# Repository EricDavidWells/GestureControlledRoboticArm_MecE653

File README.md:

# Realtime Force Myography
Using the gesture controlled robotic arm developed at [HACKED2019](https://github.com/MarkSherstan/HACKED2019) the project advanced to optimize a force myography (FMG) sensor and algorithm package that can be used to robustly control upper limb prosthetics in real time.

## Background
Although there are many multifunctional hands available for prosthesis use, commercial devices are unable to utilize them largely due to restricted control interfaces. Recent research has focused on improving pattern recognition algorithms to decode electromyographic signals (EMG) into multi degree of freedom movements to enable more robust control. Although results are promising in laboratory conditions, this technique has been unable to be transferred into commercial devices. This is largely due to current surface mounted EMG sensors having inherent unpredictable issues that affect the algorithm’s performance such as cross-talk, electrical interference, muscle fatigue effects, perspiration effects, and skin impedance. An alternative to this technology for use in prosthetics is force myography (FMG). This technology seeks to exploit the deformation resulting from residual muscle movement to obtain prosthesis control. This is typically done in a very similar manner to EMG; however, instead of measuring electrical activity, an array of pressure sensors wrapped around the user’s arm measures muscle deformation. The measured sensor values act as inputs into a pattern recognition algorithm to predict the desired motions from the user. An FMG sensor and algorithm package was designed and optimized to implement robust, real time control of a simulated prosthetic device. Two iterations of prototyping have been achieved, with the second design resulting in a wireless, low profile wristband containing 11 force sensitive resistors (FSR) sensors and an inertial measurement unit (IMU) capable of sampling up to 200 Hz.

## Photos
### Wireless Armband with 11 FSR's, IMU, and Custom PCB
<p align="center">

### Coordinate Frame on Arm
<p align="center">

### Gestures
<p align="center">

### Raw Signals (Left Time Series - Right Spectral Series)
<p align="center">

### Classified Signals PCA Representation 
<p align="center">

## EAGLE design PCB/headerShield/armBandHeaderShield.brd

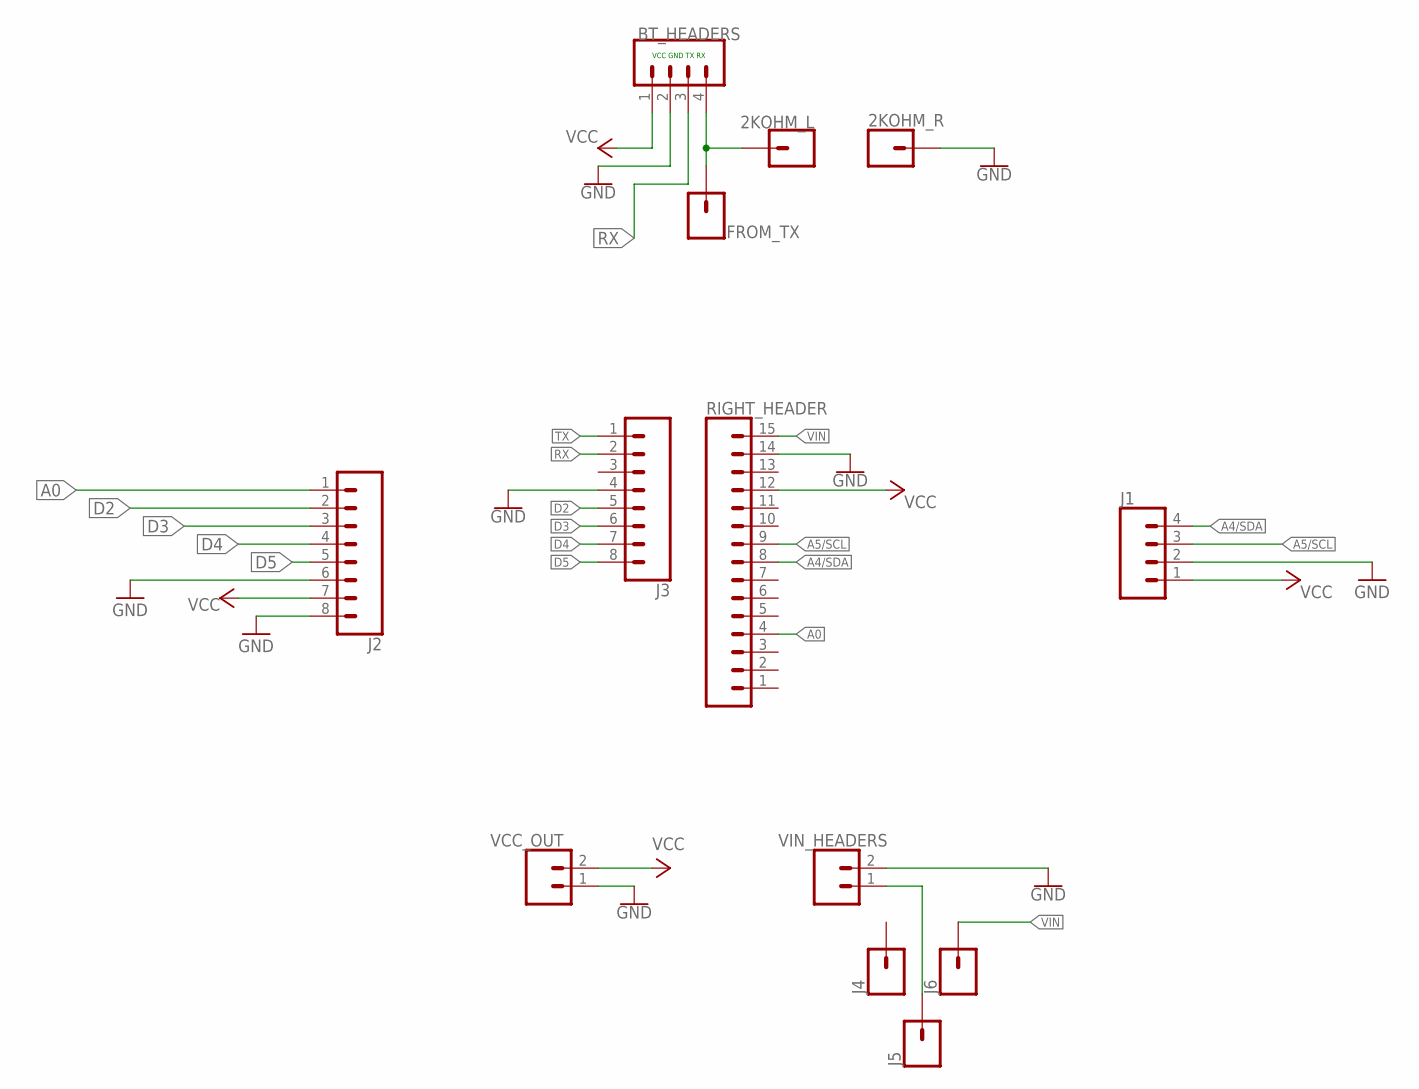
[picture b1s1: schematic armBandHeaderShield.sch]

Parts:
2KOHM_L, 2KOHM_R: CONN_01; 1X01
BT_HEADERS: CONN_04; 1X04
FROM_TX: CONN_01; 1X01
J1: CONN_04; 1X04
J2, J3: CONN_08"; 1X08
J4, J5, J6: CONN_01; 1X01
RIGHT_HEADER: CONN_15; 1X15
VCC_OUT: CONN_02PTH3; 1X02_LONGPADS
VIN_HEADERS: CONN_02PTH3; 1X02_LONGPADS

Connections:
A0: J2.1, RIGHT_HEADER.4
A4/SDA: J1.4, RIGHT_HEADER.8
A5/SCL: J1.3, RIGHT_HEADER.9
D2: J2.2, J3.5
D3: J2.3, J3.6
D4: J2.4, J3.7
D5: J2.5, J3.8
GND: 2KOHM_R.1, BT_HEADERS.2, J1.2, J2.6, J2.8, J3.4, RIGHT_HEADER.14, VCC_OUT.1, VIN_HEADERS.2
unnamed: J5.1, VIN_HEADERS.1
unnamed: 2KOHM_L.1, BT_HEADERS.4, FROM_TX.1
RX: BT_HEADERS.3, J3.2
TX: J3.1
VCC: BT_HEADERS.1, J1.1, J2.7, RIGHT_HEADER.12, VCC_OUT.2
VIN: J6.1, RIGHT_HEADER.15

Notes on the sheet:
VCC GND TX RX

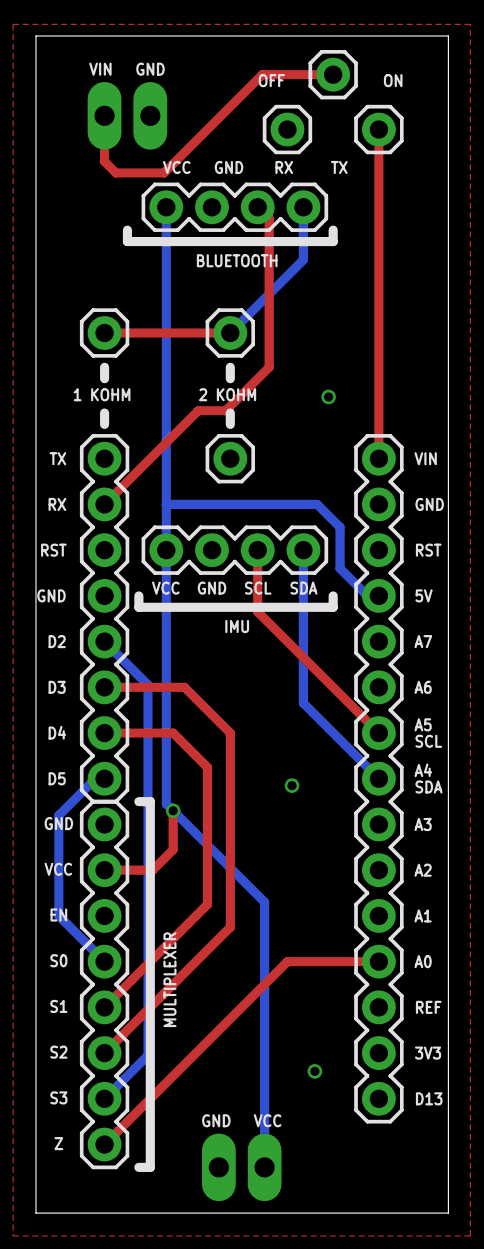
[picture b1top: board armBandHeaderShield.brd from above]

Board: 2 copper layers, 22.9 x 65.4 mm, 13 parts (0 on the bottom side), 13 nets.

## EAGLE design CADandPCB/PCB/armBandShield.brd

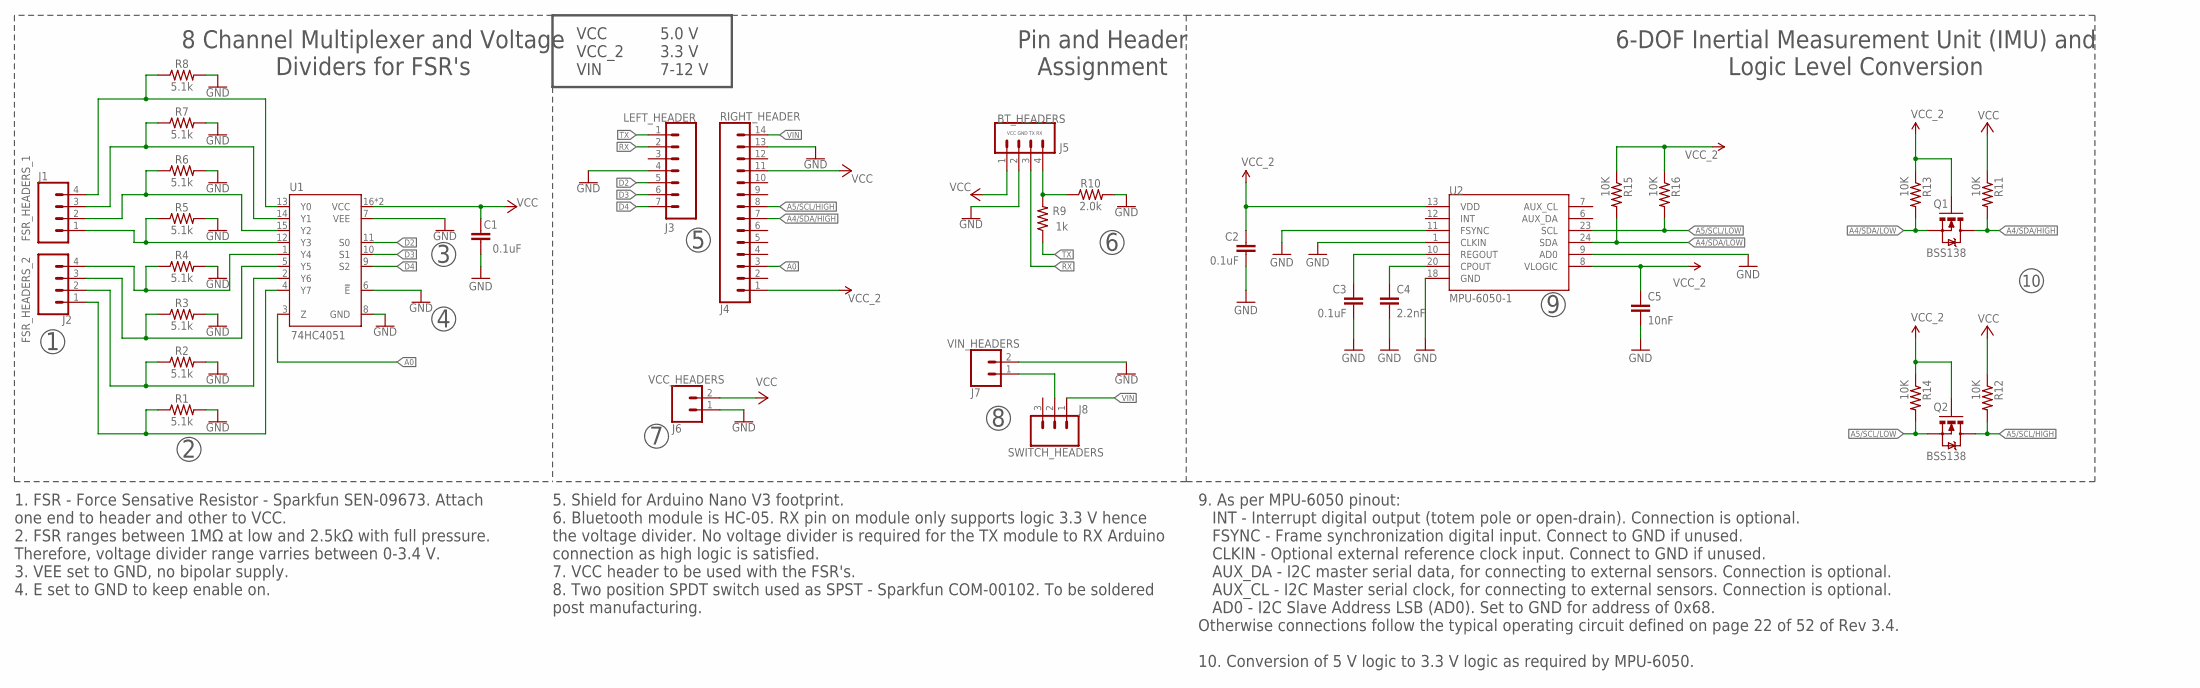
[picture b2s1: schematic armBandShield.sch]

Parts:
74HC4051: U1; DHVQFN-16-2.5X3.5MM
BT_HEADERS: J5; 1X04
C1, C2, C3: 0.1uF; 0603-CAP
C4: 2.2nF; 0603
C5: 10nF; 0603
J1: FSR_HEADERS_1; 1X04
J2: FSR_HEADERS_2; 1X04
LEFT_HEADER: J3; 1X07
Q1, Q2: BSS138; SOT23-3
R1, R2, R3, R4, R5, R6, R7, R8: 5.1k; 0603
R9: 1k; 0603
R10: 2.0k; 0603
R11, R12, R13, R14, R15, R16: 10K; 0603-RES
RIGHT_HEADER: J4; 1X14
SWITCH_HEADERS: J8; 1X03
U2: MPU-6050-1; QFN-24-4MM2
VCC_HEADERS: J6; 1X02_LONGPADS
VIN_HEADERS: J7; 1X02_LONGPADS

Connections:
A0: 74HC4051.3 (Z), RIGHT_HEADER.3
A4/SDA/HIGH: Q1.3 (D), R11.2, RIGHT_HEADER.7
A4/SDA/LOW: Q1.2 (S), R13.2, R15.2, U2.24 (SDA)
A5/SCL/HIGH: Q2.3 (D), R12.2, RIGHT_HEADER.8
A5/SCL/LOW: Q2.2 (S), R14.2, R16.2, U2.23 (SCL)
D2: 74HC4051.11 (S0), LEFT_HEADER.5
D3: 74HC4051.10 (S1), LEFT_HEADER.6
D4: 74HC4051.9 (S2), LEFT_HEADER.7
FSR1: 74HC4051.4 (Y7), J2.1, R1.1
FSR2: 74HC4051.2 (Y6), J2.2, R2.1
FSR3: 74HC4051.5 (Y5), J2.3, R3.1
FSR4: 74HC4051.1 (Y4), J2.4, R4.1
FSR5: 74HC4051.12 (Y3), J1.1, R5.1
FSR6: 74HC4051.15 (Y2), J1.2, R6.1
FSR7: 74HC4051.14 (Y1), J1.3, R7.1
FSR8: 74HC4051.13 (Y0), J1.4, R8.1
GND: 74HC4051.6 (!E!), 74HC4051.7 (VEE), 74HC4051.8 (GND), BT_HEADERS.2, C1.2, C2.2, C3.2, C4.2, C5.2, LEFT_HEADER.4, R1.2, R2.2, R3.2, R4.2, R5.2, R6.2, R7.2, R8.2, R10.2, RIGHT_HEADER.13, U2.1 (CLKIN), U2.9 (AD0), U2.11 (FSYNC), U2.18 (GND), VCC_HEADERS.1, VIN_HEADERS.2
unnamed: SWITCH_HEADERS.2, VIN_HEADERS.1
unnamed: C4.1, U2.20 (CPOUT)
unnamed: C3.1, U2.10 (REGOUT)
unnamed: BT_HEADERS.4, R9.2, R10.1
RX: BT_HEADERS.3, LEFT_HEADER.2
TX: LEFT_HEADER.1, R9.1
VCC: 74HC4051.16 (VCC), 74HC4051.EP (VCC), BT_HEADERS.1, C1.1, R11.1, R12.1, RIGHT_HEADER.11, VCC_HEADERS.2
VCC_2: C2.1, C5.1, Q1.1 (G), Q2.1 (G), R13.1, R14.1, R15.1, R16.1, RIGHT_HEADER.1, U2.8 (VLOGIC), U2.13 (VDD)
VIN: RIGHT_HEADER.14, SWITCH_HEADERS.1

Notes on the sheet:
VCC GND TX RX
8 Channel Multiplexer and Voltage Dividers for FSR's
1. FSR - Force Sensative Resistor - Sparkfun SEN-09673. Attach one end to header and other to VCC. 2. FSR ranges between 1MΩ at low and 2.5kΩ with full pressure. Therefore, voltage divider range varries between 0-3.4 V. 3. VEE set to GND, no bipolar supply. 4. E set to GND to keep enable on.
Pin and Header Assignment
6-DOF Inertial Measurement Unit (IMU) and Logic Level Conversion
5. Shield for Arduino Nano V3 footprint. 6. Bluetooth module is HC-05. RX pin on module only supports logic 3.3 V hence the voltage divider. No voltage divider is required for the TX module to RX Arduino connection as high logic is satisfied. 7. VCC header to be used with the FSR's. 8. Two position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
VCC VCC_2 VIN
5.0 V 3.3 V 7-12 V
9. As per MPU-6050 pinout: INT - Interrupt digital output (totem pole or open-drain). Connection is optional. FSYNC - Frame synchronization digital input. Connect to GND if unused. CLKIN - Optional external reference clock input. Connect to GND if unused. AUX_DA - I2C master serial data, for connec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

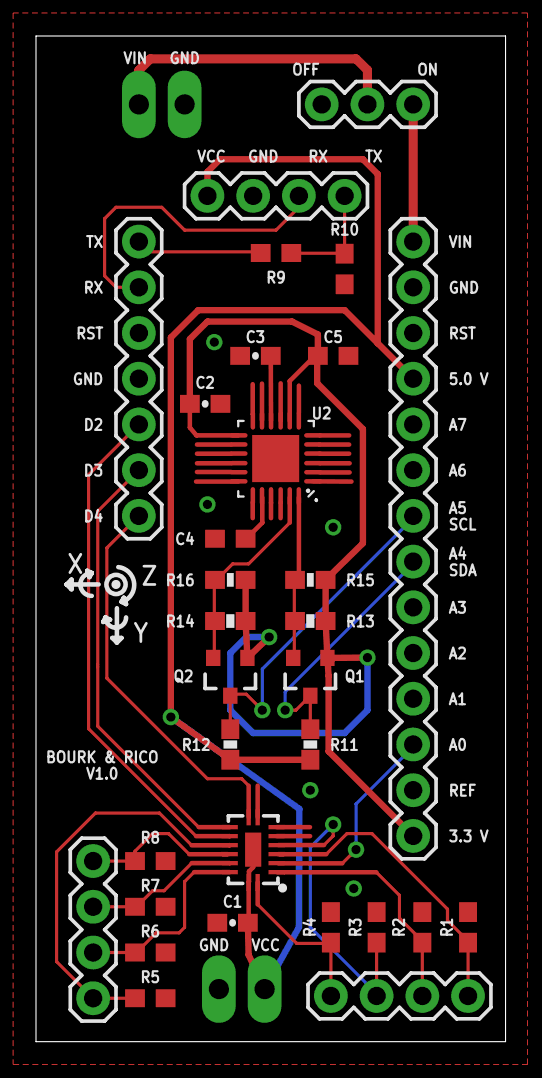
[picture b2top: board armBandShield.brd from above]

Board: 2 copper layers, 26.1 x 55.9 mm, 33 parts (0 on the bottom side), 26 nets.

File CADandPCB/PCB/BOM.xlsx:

Designator | Value | Manufacturer Part # | DIGI-KEY Part # | Qty | Cost / Unit | % Extra | Total Qty | Total Cost | Notes | Link
R1,R2,R3,R4,R5,R6,R7,R8 | 5.1 k | ERJ-3EKF5101V | P5.10KHCT-ND | 8 | 9.8000000000000004E-2 | 5 | 40 | 3.92 | Price Break! | https://www.digikey.ca/product-detail/en/ERJ-3EKF5101V/P5.10KHCT-ND
R9 | 1 k | ERJ-3EKF1001V | P1.00KHCT-ND | 1 | 9.8000000000000004E-2 | 10 | 10 | 0.98 | Price Break! | https://www.digikey.ca/product-detail/en/ERJ-3EKF1001V/P1.00KHCT-ND
R10 | 2 k | ERJ-3EKF2001V | P2.00KHCT-ND | 1 | 9.8000000000000004E-2 | 10 | 10 | 0.98 | Price Break! | https://www.digikey.ca/product-detail/en/ERJ-3EKF2001V/P2.00KHCT-ND
R11,R12,R13,R14,R15,R16 | 10 k | ERJ-3EKF1002V | P10.0KHCT-ND | 6 | 9.8000000000000004E-2 | 8 | 48 | 4.7040000000000006 | Price Break! | https://www.digikey.ca/product-detail/en/ERJ-3EKF1002V/P10.0KHCT-ND
C1,C2,C3 | 0.1 uF | CL10B104KB8NNNC | 1276-1000-1-ND | 3 | 4.7E-2 | 7 | 21 | 0.98699999999999999 | Price Break! | https://www.digikey.ca/product-detail/en/CL10B104KB8NNNC/127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
C4 | 2.2 nF | CL10B222JB8NNNC | 1276-1987-1-ND | 1 | 0.06 | 10 | 10 | 0.6 | Price Break! | https://www.digikey.ca/product-detail/en/CL10B222JB8NNNC/127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
C5 | 10 nF | CL10B103KB8NNNC | 1276-1009-1-ND | 1 | 5.1999999999999998E-2 | 10 | 10 | 0.52 | Price Break! | https://www.digikey.ca/product-detail/en/CL10B103KB8NNNC/127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
Q1,Q2 | - | BSS138 | BSS138CT-ND | 2 | 0.39600000000000002 | 5 | 10 | 3.96 | Price Break! | https://www.digikey.ca/product-detail/en/on-semiconductor/BS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
U1 | - | 74HC4051BQ,115 | 1727-6049-1-ND | 1 | 0.58799999999999997 | 10 | 10 | 5.88 | Price Break! | https://www.digikey.ca/product-detail/en/nexperia-usa-inc/74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
U2 | - | MPU-6050 | 1428-1007-1-ND | 1 | 11.007999999999999 | 5 | 5 | 55.039999999999992 | Price Break! | https://www.digikey.ca/product-detail/en/tdk-invensense/MPU-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
 |  |  |  |  |  |  | Total | 77.570999999999998
Other | Qty | Cost / Unit | Total Cost | Link
MPU 6050 breakout!! | 1 | 14.47 | 14.47 | https://www.digikey.ca/product-detail/en/dfrobot/SEN0142/173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
 | 2 | 12.05 | 24.1 | https://www.digikey.ca/product-detail/en/trinamic-motion-con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
 | 1 | 30.13 | 30.13 | https://www.digikey.ca/product-detail/en/trinamic-motion-con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
 |  | Total | 68.7
$100 Free Shipping
HC-05????
FSR
10^-6 micro µ | 0.0022 pF
10^-9 nano n | 2.2 nF
10^-12 pico p | 2200 uF

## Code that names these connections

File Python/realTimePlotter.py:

# Adapted from: https://www.thepoorengineer.com/en/arduino-python-plot/
from threading import Thread
import serial
import time
import collections
import matplotlib.pyplot as plt
import matplotlib.animation as animation
import struct
import copy


class serialPlot:
    def __init__(self, serialPort, serialBaud, plotLength, dataNumBytes, numSignals):
        self.port = serialPort
        self.baud = serialBaud
        self.plotMaxLength = plotLength
        self.dataNumBytes = dataNumBytes
        self.numSignals = numSignals
        self.rawData = bytearray(numSignals * dataNumBytes)
        self.dataType = None

        if dataNumBytes == 2:
            self.dataType = 'h'

        self.data = []
        for i in range(numSignals):
            self.data.append(collections.deque([0] * plotLength, maxlen=plotLength))

        self.isRun = True
        self.isReceiving = False
        self.thread = None
        self.plotTimer = 0
        self.previousTimer = 0

        print('Trying to connect to: ' + str(serialPort) + ' at ' + str(serialBaud) + ' BAUD.')
        try:
            self.serialConnection = serial.Serial(serialPort, serialBaud, timeout=4)
            print('Connected to ' + str(serialPort) + ' at ' + str(serialBaud) + ' BAUD.')
        except:
            print("Failed to connect with " + str(serialPort) + ' at ' + str(serialBaud) + ' BAUD.')

    def readSerialStart(self):
        if self.thread == None:
            self.thread = Thread(target=self.backgroundThread)
            self.thread.start()
            # Block till we start receiving values
            while self.isReceiving != True:
                time.sleep(0.1)

    def getSerialData(self, frame, lines, lineValueText, lineLabel, timeText):
        currentTimer = time.perf_counter()
        self.plotTimer = int((currentTimer - self.previousTimer) * 1000)
        self.previousTimer = currentTimer
        timeText.set_text('Plot Interval = ' + str(self.plotTimer) + ' ms')
        privateData = copy.deepcopy(self.rawData[:])
        for i in range(self.numSignals):
            data = privateData[(i*self.dataNumBytes):(self.dataNumBytes + i*self.dataNumBytes)]
            value,  = struct.unpack(self.dataType, data)
            self.data[i].append(value)
            lines[i].set_data(range(self.plotMaxLength), self.data[i])
            lineValueText[i].set_text('[' + lineLabel[i] + '] = ' + str(value))

    def backgroundThread(self):
        time.sleep(2)
        self.serialConnection.reset_input_buffer()

        while (self.isRun):
            if (struct.unpack('B', self.serialConnection.read())[0] is 0x9F) and (struct.unpack('B', self.serialConnection.read())[0] is 0x6E):
                self.rawData = self.serialConnection.read(self.numSignals * self.dataNumBytes)
                self.isReceiving = True

    def close(self):
        self.isRun = False
        self.thread.join()
        self.serialConnection.close()
        print('Disconnected...')



def main():
    portName = '/dev/cu.wchusbserial1410'
    baudRate = 115200
    maxPlotLength = 100
    dataNumBytes = 2
    numSignals = 8

    s = serialPlot(portName, baudRate, maxPlotLength, dataNumBytes, numSignals)
    s.readSerialStart()

    pltInterval = 20
    xmin = 0
    xmax = maxPlotLength
    ymin = 0
    ymax = 1024

    fig = plt.figure(figsize=(12, 6))
    ax = plt.axes(xlim=(xmin, xmax), ylim=(float(ymin - (ymax - ymin) / 10), float(ymax + (ymax - ymin) / 10)))
    ax.set_title("FSR Live Output",fontweight='bold',size=20)
    ax.set_xlabel("Time -->",fontweight='bold')
    ax.set_ylabel("Raw Analog Out",fontweight='bold')

    lineLabel = ['FSR1', 'FSR2', 'FSR3', 'FSR4', 'FSR5', 'FSR6', 'FSR7', 'FSR8']
    style = ['c-', 'm-', 'y-', '-k', '--c', '--m', '--y', '--k']
    timeText = ax.text(0.80, 0.95, '', transform=ax.transAxes)
    lines = []
    lineValueText = []
    for i in range(numSignals):
        lines.append(ax.plot([], [], style[i], label=lineLabel[i])[0])
        lineValueText.append(ax.text(0.05, 0.95-i*0.05, '', transform=ax.transAxes))

    anim = animation.FuncAnimation(fig, s.getSerialData, fargs=(lines, lineValueText, lineLabel, timeText), interval=pltInterval)    # fargs has to be a tuple

    plt.legend(loc='upper center', ncol=4)
    plt.xticks([])
    plt.show()

    s.close()


if __name__ == '__main__':
    main()

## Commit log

2019-01-28 Added Training Function and Data Visualization Function
2019-01-28 Added main script to call all functions
2019-01-28 Remove .asv files and make .gitignore
2019-01-28 Servo kill switch, display messages, readability
2019-01-28 General cleanup
2019-01-28 Add stateVisualizer to display the state instead of command line.
2019-01-28 Performance increase for visualizer.
2019-01-28 Fix ... and \c warning in main and training functions
2019-01-28 Added variable classes to visualize data
2019-02-05 Add component data sheets for pinout.
2019-02-06 Commit 9250 data sheet
2019-02-15 Initial commit of Eagle files
2019-02-16 Commit robotArm printing resources
2019-02-16 Add eagle backup to gitignore.
2019-02-16 Clean up schematic using labels. Remove old board. Prepare for breakout.
2019-02-16 Added required breakout components for MPU 9250
2019-02-16 Added required breakout components for Multixplexer
2019-02-16 Initial board lay out and .brd commit
2019-02-16 Clean up silk screen and add ground plane.
2019-02-17 Sliced remaining files and added hardware list.
2019-02-17 All connections routed
2019-02-17 Increase solder pad lengths for chips
2019-02-17 Begin performing DRC checks
2019-02-17 Rev 1 board completed. Performed checks and added headers for switch.
2019-02-18 Added .pro files from Eagle autorouter.
2019-02-18 Designed a board for headers / brkt board to manufacture at engg garage.
2019-02-18 Updated print log
2019-02-19 Add new IMU and logical level data sheets.
2019-02-19 Replace MPU-9250 with MPU-6050. Added logic level. Cleaned up schematic.
2019-02-19 Added reference designators and double checked entire schematic.
2019-02-19 Initial layout 95% complete
2019-02-19 Board V2 Completed.
2019-02-19 Offset swtich headers.
2019-02-19 Updated part tracker with all printing.
2019-02-21 Initial commit of Python script for controlling 4-dof robot arm.
2019-02-21 Initial commit of IMU with a comp filter.
2019-02-21 Commit bluetooth AT configuration sketch with current values.
2019-03-02 Added data loading and visualization
2019-03-03 Added SVM classifier prediction
2019-03-04 Added serial to python, changed how arduino reads serial
2019-03-04 Update trace sizes, pad extensions, silkscreen, and some routing.
2019-03-04 Double checked schematic and moved a few traces for asthetics.
2019-03-05 Increase tstop and tcream
2019-03-05 Commit Gerber files and final rev 1 of board.
2019-03-05 Commit Gerber files and final rev 1 for the header version of board.
2019-03-06 Initial commit serial plotter
2019-03-06 Initial commit - removed all plotting refernces.
2019-03-06 Got rid of threads
    Running at approximately 200 Hz
2019-03-07 Cleaned up python and attempting header for accurate parsing.
2019-03-07 Added header check
2019-03-07 Offering Alternative to Mark's Garbo
2019-03-07 Optimized the time sync for 200 Hz
2019-03-07 Add python link with bytes
2019-03-07 Comment out calibration portion
2019-03-07 Initial commit of Python script to plot angles from filter, gyro, accel
2019-03-08 Integrated serialComs into main for one way coms
    Running at 160Hz on my home pc
2019-03-08 Added getting training data function
2019-03-08 Added shield directory
2019-03-08 create armband directory
2019-03-08 Moved data sheet folder
2019-03-08 Commit PCB BOM and add gerbers to shield folder
2019-03-08 Update BOM and data sheets
2019-03-08 Move robot arm to newest python folder.
2019-03-09 Update IMU sketch to only read I2C and send bytes over serial.
2019-03-09 Begin treansfer from Arduino to python. Wrote gyro calibration function.
2019-03-10 Fix order of gyro / accel byte writing
2019-03-10 Write function for reading IMU and procesing the values to be usable
2019-03-10 Added a comp filter function
2019-03-10 Commit class for IMU
2019-03-10 Fix nonetype error when bytes arent in buffer.
2019-03-10 Remove test sketch and old serial writer.
2019-03-10 Completly rewrote multiplexer code.
2019-03-10 Remove sketch used for testing serial port and FSR's.See multiplexer now
2019-03-10 Move the serial plotter with multiplexer and tested.
2019-03-10 remove ardiuno sketch for serial plotter. Refer to multiplexer.
2019-03-11 Update directory and rename file
2019-03-11 Rewrite main to include updated IMU and multiplexer sketches in one.
2019-03-11 Initial commit of main.py for reading IMU and FSR's in Python.
2019-03-11 Fixed tau variable def and FSR force calculation. Tested and verified.
2019-03-11 Changed real time plotter from analog plotting to force plotting.
2019-03-11 Rename and redirect real time plotter back to multiplexer dir.
2019-03-11 Add FSR data sheet.
2019-03-11 Formatted, added comments, changed plot to include time.
2019-03-11 Added comments and some formatting.
2019-03-11 Added comments
2019-03-17 Add end effector CAD files.
2019-03-17 Add name tag and update FSR mount
2019-03-19 Update full scale range to 2g and 250 deg/s --> 0x00
2019-03-19 Add RPi data sheet
2019-03-31 Added 3 analog pins and a couple lines to print ASCII values to serial.
2019-03-31 Send additional sensor data to Python and add footer hexadecimal bytes.
2019-03-31 Added footer check and the extra FSR's. Running a little slow.
2019-03-31 Add extra FSR's and footer.
2019-03-31 Add extra FSR sensors and footer check.
2019-04-01 Commit updated armband Solidworks Files.
2019-04-01 Working version for RPi 3B+
2019-04-01 Initial commit RPi 3B+ and HC-05 setup and pairing guide.
2019-04-01 Update README with formatting and some better clarification.
2019-04-05 Add data logging to CSV file.
2019-04-05 Initial commit of a filter designer.
2019-04-05 Minor updates from progress report
2019-04-06 Round print to 2 sig dig screen for FSR and angles.
2019-04-07 Added model class
    model class and real time updates into main script
2019-04-07 Updated and added robot arm control class and tested
2019-04-07 Commit ricos unbelievable blundering errors
2019-04-07 Fixed data out checks
2019-04-07 Added threading, trainSVM model, spaghetti
2019-04-07 Created pickles object saving and small clean up.
2019-04-07 Commit test data
2019-04-07 Commit more test data with IMU
2019-04-07 Fixed sampling rate issue to confirm 200 Hz
2019-04-07 Minor filter design updates
2019-04-07 Back up to something that works and troubleshoot.
2019-04-07 Commit some data for real time control
2019-04-07 Clean up the filtering and data writing.
2019-05-08 simple regression and classification scripts using pygame
2019-06-01 Add comments and delete commented blocks.
2019-06-01 Commit numberDemo, rico, and test.py sketches from local to git.
2019-06-03 Commit file from RPi
2019-06-03 Commit demo script used in presentations from off the RPi.
2019-11-06 super well thought out changes, easy to follow, nothing more to be said
2019-11-06 Remove data
2019-11-06 Remove CAD and create single PCB folder.
2019-11-06 MERKeD maTLaB
2019-11-06 Finalized PCB directory.
2019-11-06 more merks
2019-11-06 Cleaning up the chopped leaf
2019-11-07 narrowed down culprits to 5 files
2019-11-07 Remove .idea folder cause its a bad idea.
2019-11-07 folder changes
2019-11-07 more files removed
2019-11-07 Add demo class for visual and robot arm.
2019-11-07 added serial class, minor adjustments to confirm number demo worked
2019-11-07 file name changes
2019-11-07 fixed thread exiting
2019-11-07 Fix import options for running on Pi
2019-11-13 Updated working Pi code
2019-11-13 minor clean up
2019-11-13 minor changes
2020-01-14 Added realtime visualization of raw FSR values for debugging

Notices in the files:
parts and their libraries:
SparkFun-Connectors: Licensing: Creative Commons ShareAlike 4.0 International - https://creativecommons.org/licenses/by-sa/4.0
